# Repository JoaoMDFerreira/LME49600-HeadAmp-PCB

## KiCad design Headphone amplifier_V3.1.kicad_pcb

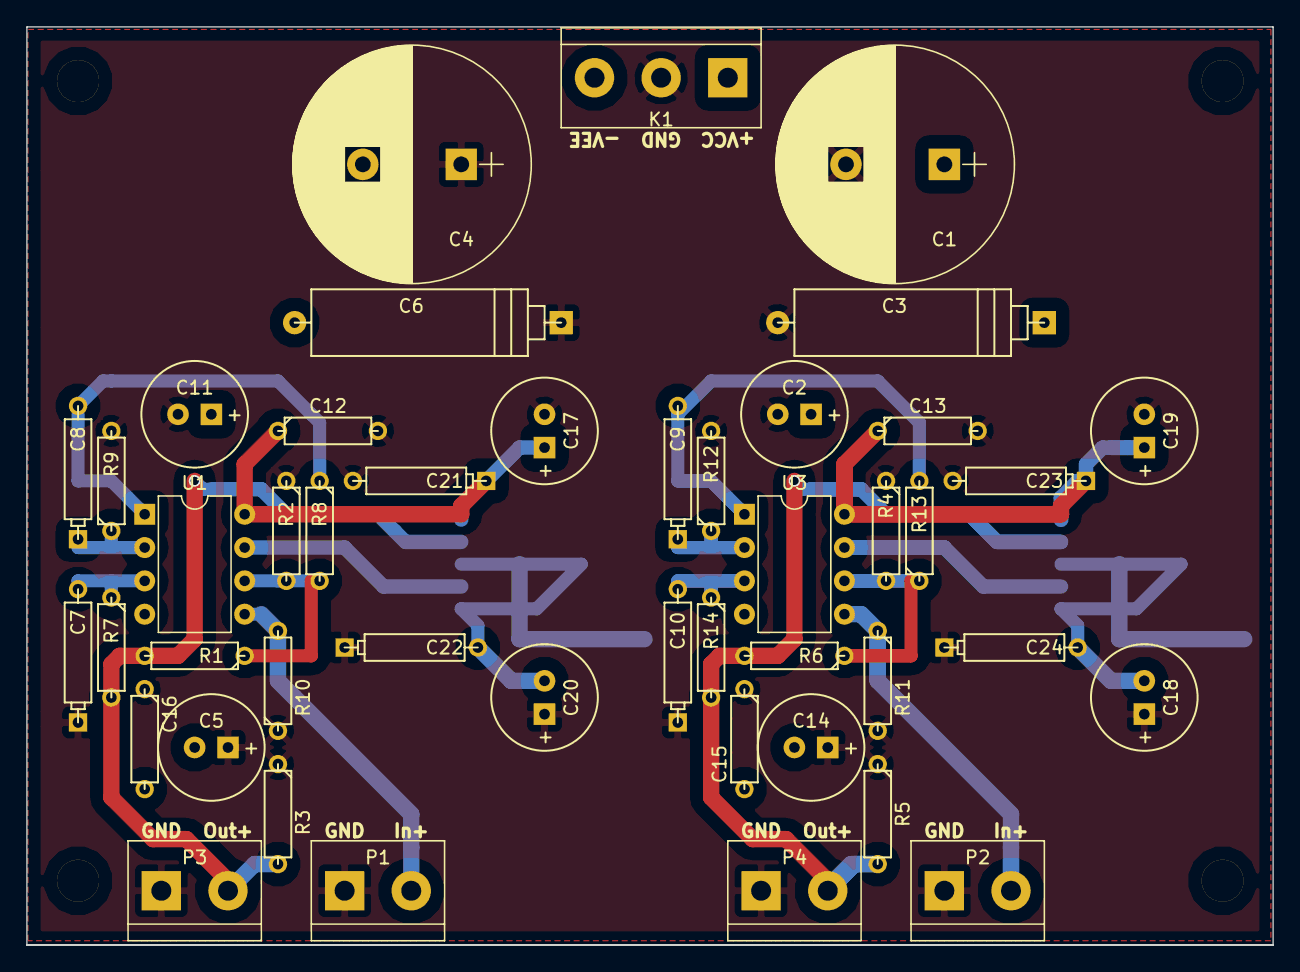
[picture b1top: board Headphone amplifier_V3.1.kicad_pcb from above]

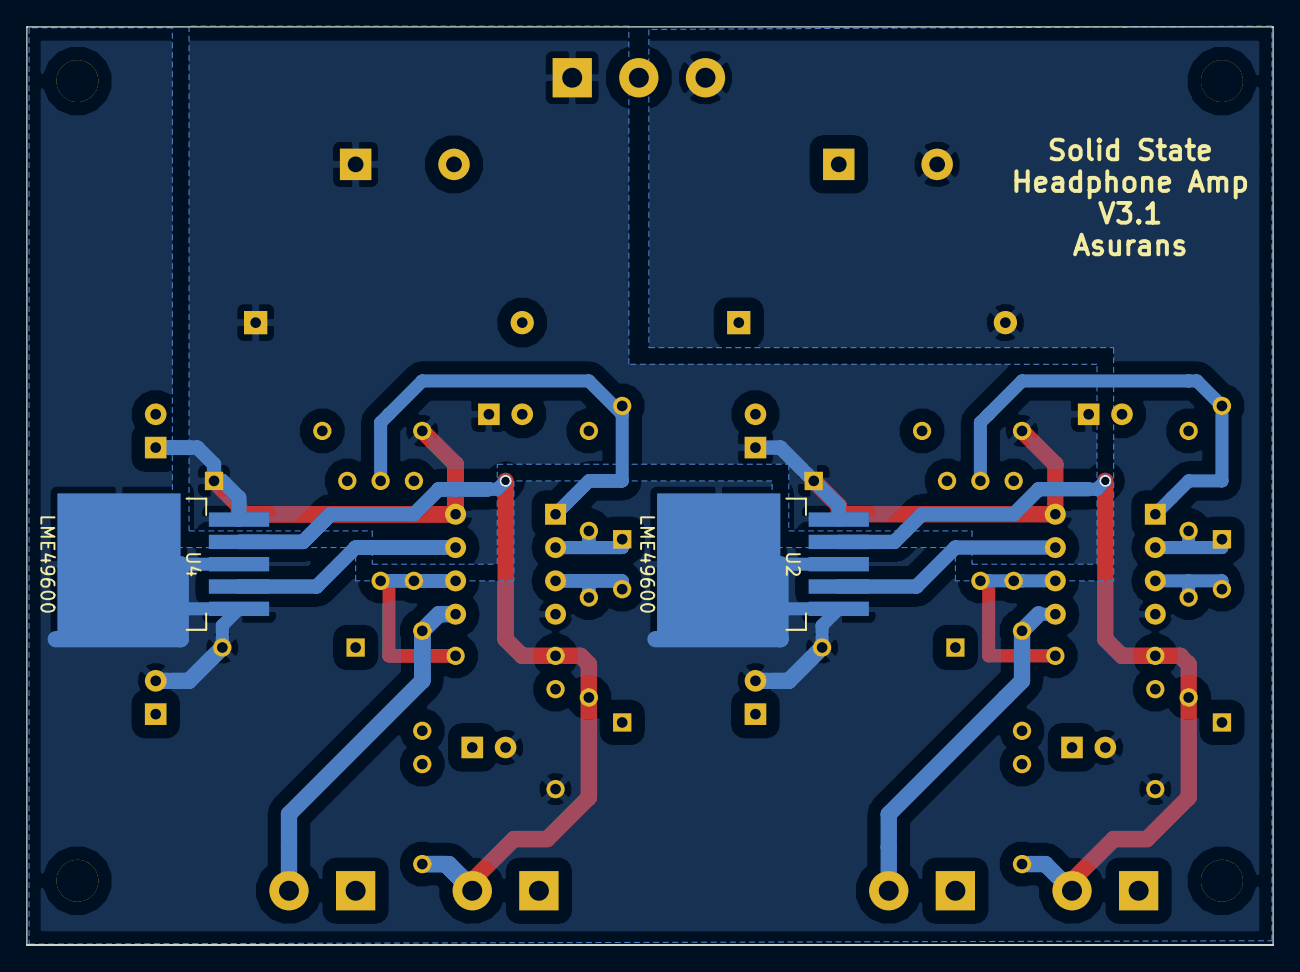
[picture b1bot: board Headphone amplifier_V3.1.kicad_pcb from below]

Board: 2 copper layers, 95.0 x 70.0 mm, 47 parts (2 on the bottom side), 17 nets.

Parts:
C1, C4: 4700u; CP_Radial_D18.0mm_P7.50mm
C2, C5, C11, C14, C17, C18, C19, C20: 47u; C1V8
C3, C6: 8200p; CP8
C7, C8, C9, C10: 1u; CP4
C12, C13, C15, C16: 100n; R3
C21, C22, C23, C24: 22u; CP4
K1: CONN_3; bornier3
P1, P2, P3, P4: CONN_01X02; bornier2
R1, R2, R4, R6, R8, R13: 1K; R3
R3, R5: 100K; R3
R7, R9, R12, R14: 1M; R3
R10, R11: 47K; R3
U1, U3: TL072; DIP-8_W7.62mm
U2, U4: LME49600; TO-263-5Lead

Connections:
GND: C1.2, C2.2, C3.2, C4.1, C5.1, C6.1, C7.1, C10.1, C11.2, C12.2, C13.2, C14.1, C15.1, C16.1, C17.2, C18.1, C19.2, C20.1, C21.2, C22.1, C23.2, C24.1, K1.2, P1.1, P2.1, P3.1, P4.1, R2.1, R3.1, R4.1, R5.1, R9.2, R10.1, R11.2, R12.2
unnamed: C7.2, R7.1, U1.3
unnamed: C8.1, R9.1, U1.2
unnamed: C8.2, R8.1, U1.1
unnamed: C9.1, R12.1, U3.2
unnamed: C9.2, R13.2, U3.1
unnamed: C10.2, R14.1, U3.3
unnamed: P1.2, R10.2, U1.5
unnamed: P2.2, R11.1, U3.5
unnamed: P3.2, R1.2, R3.2, R7.2, U2.4
unnamed: P4.2, R5.2, R6.2, R14.2, U4.4
unnamed: R1.1, R2.2, R8.2, U1.6
unnamed: R4.2, R6.1, R13.1, U3.6
unnamed: U1.7, U2.2
unnamed: U3.7, U4.2
VCC: C1.1, C2.1, C3.1, C11.1, C12.1, C13.1, C17.1, C19.1, C21.1, C23.1, K1.1, U1.8, U2.5, U3.8, U4.5
VEE: C4.2, C5.2, C6.2, C14.2, C15.2, C16.2, C18.2, C20.2, C22.2, C24.2, K1.3, U1.4, U2.1, U2.3, U3.4, U4.1, U4.3

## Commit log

2019-04-27 LME49600 a 720 base HeadAmp
